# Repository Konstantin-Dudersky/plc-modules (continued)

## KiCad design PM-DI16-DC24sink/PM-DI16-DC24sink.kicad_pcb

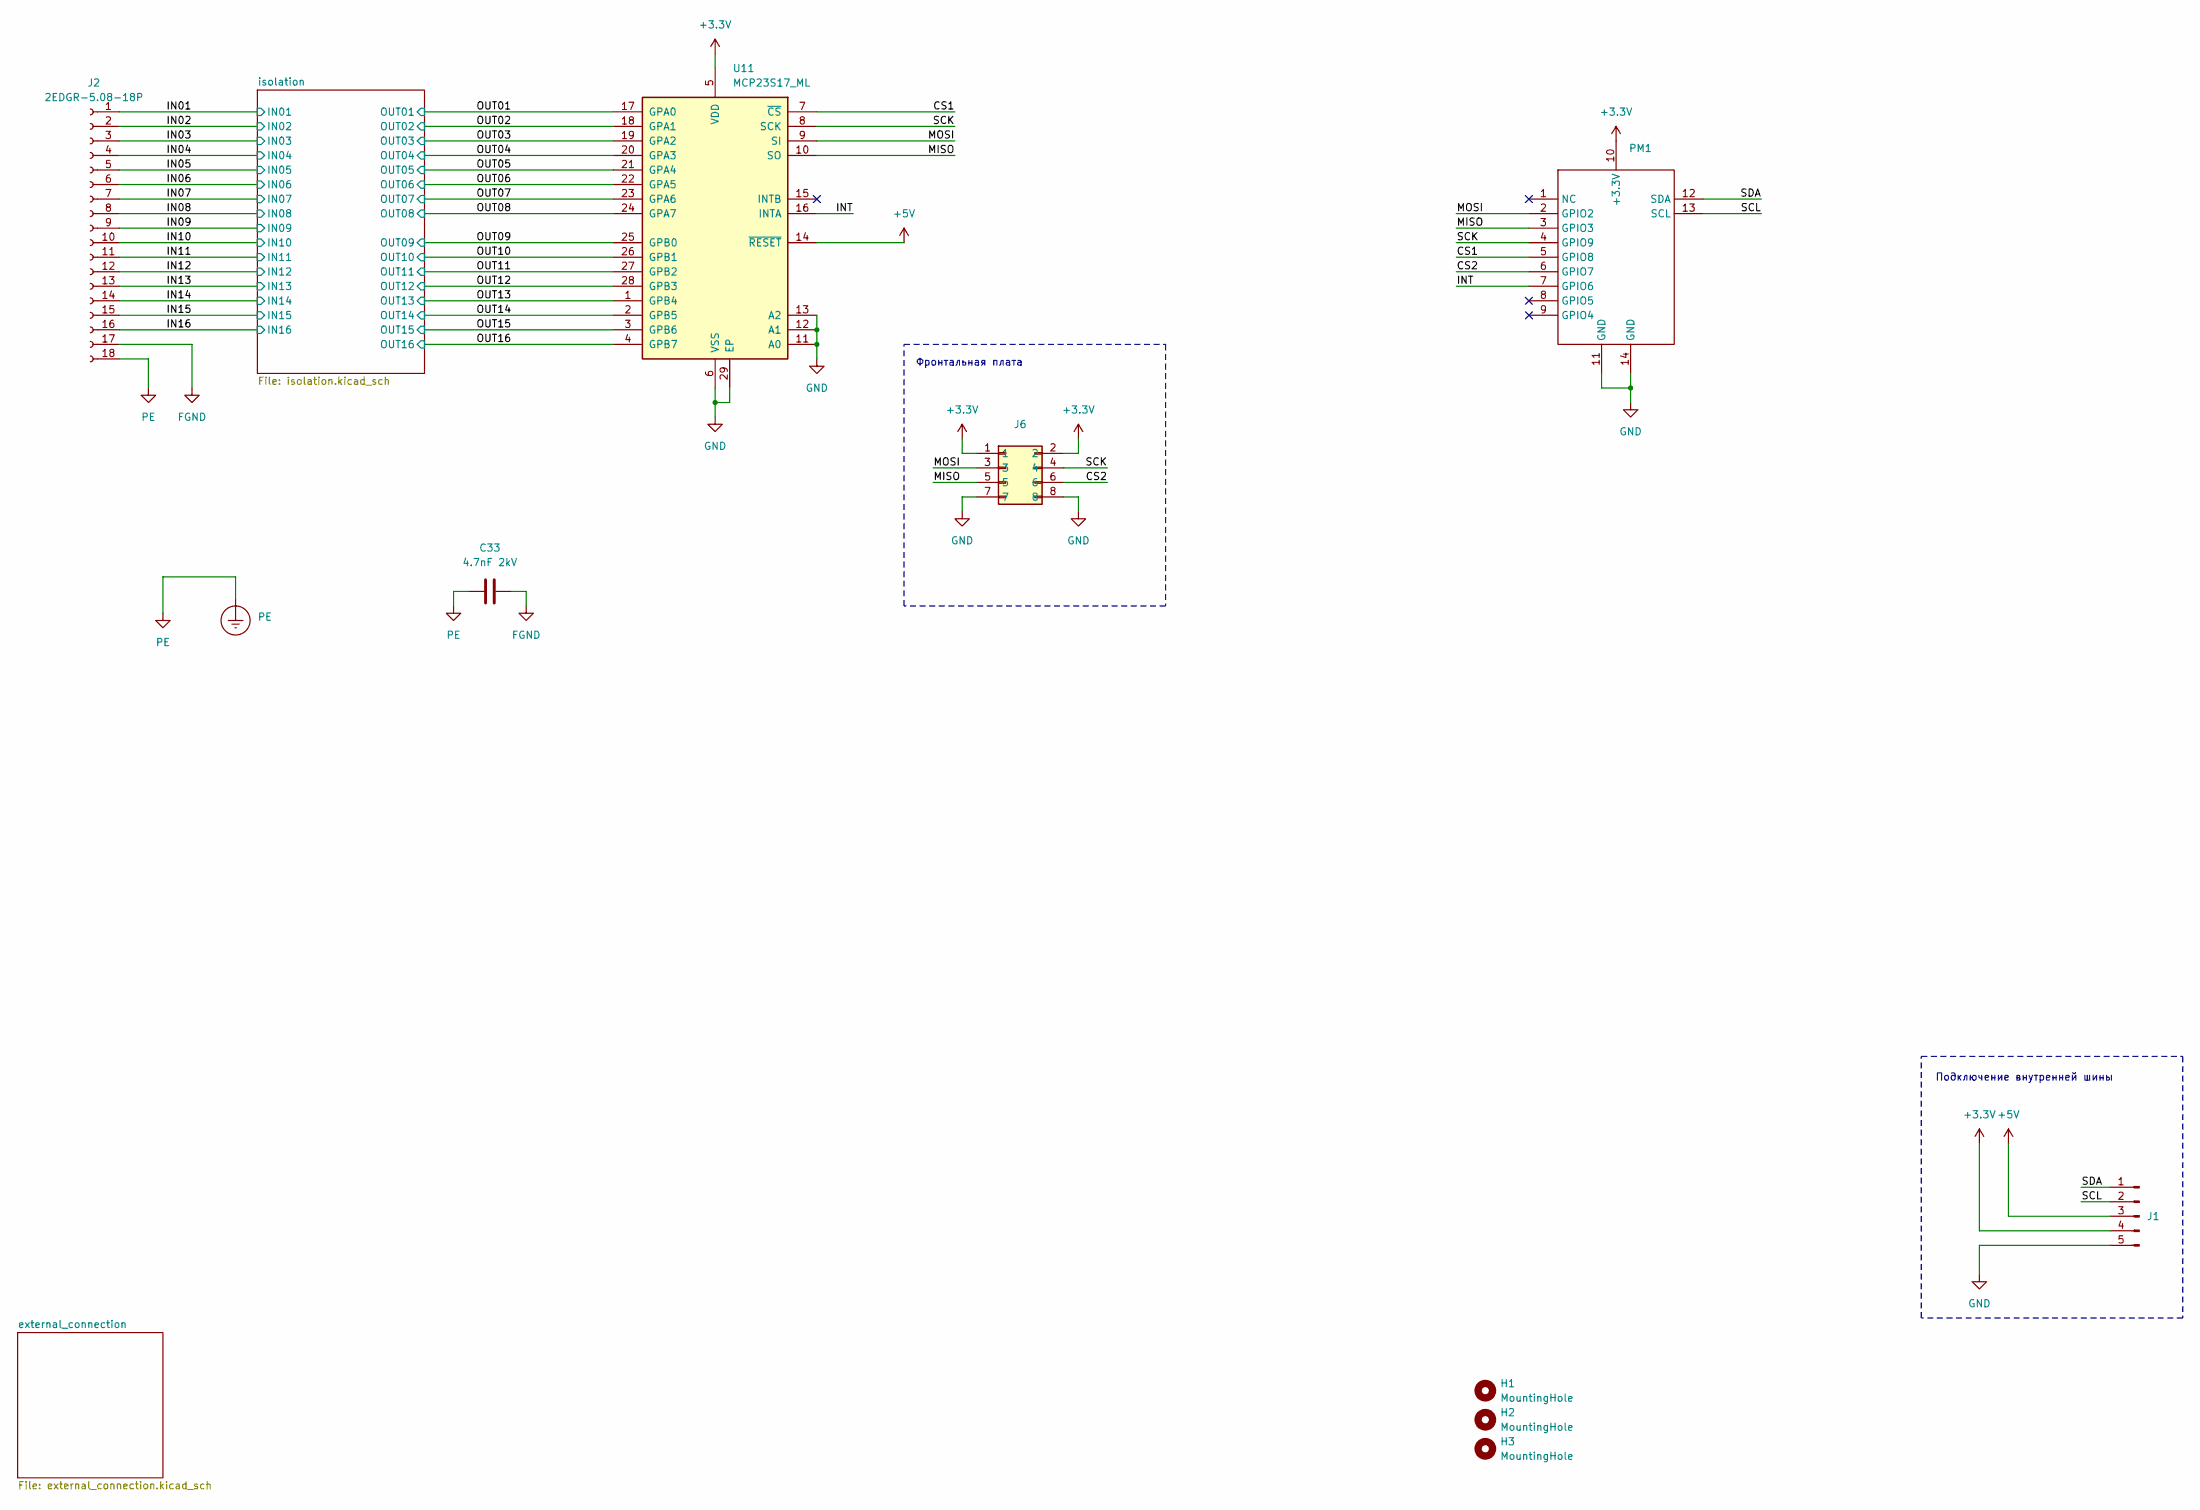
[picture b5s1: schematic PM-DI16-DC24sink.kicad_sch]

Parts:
C33: 4.7nF 2kV; C_1812_4532Metric_Pad1.57x3.40mm_HandSolder; part_ipn C_4.7nF_2kV_1812
H1, H2, H3: MountingHole; MountingHole_3.2mm_M3
J1: PinHeader_01x05_P2.54_THT_angle; PinHeader_1x05_P2.54mm_Horizontal; part_ipn PinHeader_01x05_P2.54_THT_angle
J2: 2EDGR-5.08-18P; Degson_2EDGR-5.08-18P; part_ipn 2EDGR-5.08-18P
J6: PM-front-02x04
PE1: PE
PM1: PM-ESP32C3
U11: MCP23S17_ML; QFN-28-1EP_6x6mm_P0.65mm_EP4.25x4.25mm; part_ipn MCP23S17-E/ML

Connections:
+3.3V: J1.4, J6.1, J6.2, PM1.10 (+3.3V), U11.5 (VDD)
+5V: J1.3, U11.14 (~RESET); also elsewhere on the board
/CS1: PM1.5 (GPIO8), U11.7 (~CS)
/CS2: J6.6, PM1.6 (GPIO7)
/IN01: J2.1; also elsewhere on the board
/IN02: J2.2; also elsewhere on the board
/IN03: J2.3; also elsewhere on the board
/IN04: J2.4; also elsewhere on the board
/IN05: J2.5; also elsewhere on the board
/IN06: J2.6; also elsewhere on the board
/IN07: J2.7; also elsewhere on the board
/IN08: J2.8; also elsewhere on the board
/IN09: J2.9; also elsewhere on the board
/IN10: J2.10; also elsewhere on the board
/IN11: J2.11; also elsewhere on the board
/IN12: J2.12; also elsewhere on the board
/IN13: J2.13; also elsewhere on the board
/IN14: J2.14; also elsewhere on the board
/IN15: J2.15; also elsewhere on the board
/IN16: J2.16; also elsewhere on the board
/INT: PM1.7 (GPIO6), U11.16 (INTA)
/MISO: J6.5, PM1.3 (GPIO3), U11.10 (SO)
/MOSI: J6.3, PM1.2 (GPIO2), U11.9 (SI)
/OUT01: U11.17 (GPA0); also elsewhere on the board
/OUT02: U11.18 (GPA1); also elsewhere on the board
/OUT03: U11.19 (GPA2); also elsewhere on the board
/OUT04: U11.20 (GPA3); also elsewhere on the board
/OUT05: U11.21 (GPA4); also elsewhere on the board
/OUT06: U11.22 (GPA5); also elsewhere on the board
/OUT07: U11.23 (GPA6); also elsewhere on the board
/OUT08: U11.24 (GPA7); also elsewhere on the board
/OUT09: U11.25 (GPB0); also elsewhere on the board
/OUT10: U11.26 (GPB1); also elsewhere on the board
/OUT11: U11.27 (GPB2); also elsewhere on the board
/OUT12: U11.28 (GPB3); also elsewhere on the board
/OUT13: U11.1 (GPB4); also elsewhere on the board
/OUT14: U11.2 (GPB5); also elsewhere on the board
/OUT15: U11.3 (GPB6); also elsewhere on the board
/OUT16: U11.4 (GPB7); also elsewhere on the board
/SCK: J6.4, PM1.4 (GPIO9), U11.8 (SCK)
/SCL: J1.2, PM1.13 (SCL)
/SDA: J1.1, PM1.12 (SDA)
FGND: C33.2, J2.17; also elsewhere on the board
GND: J1.5, J6.7, J6.8, PM1.11 (GND), PM1.14 (GND), U11.6 (VSS), U11.11 (A0), U11.12 (A1), U11.13 (A2), U11.29 (EP); also elsewhere on the board
PE: C33.1, J2.18, PE1.1

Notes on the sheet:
Фронтальная плата
Подключение внутренней шины

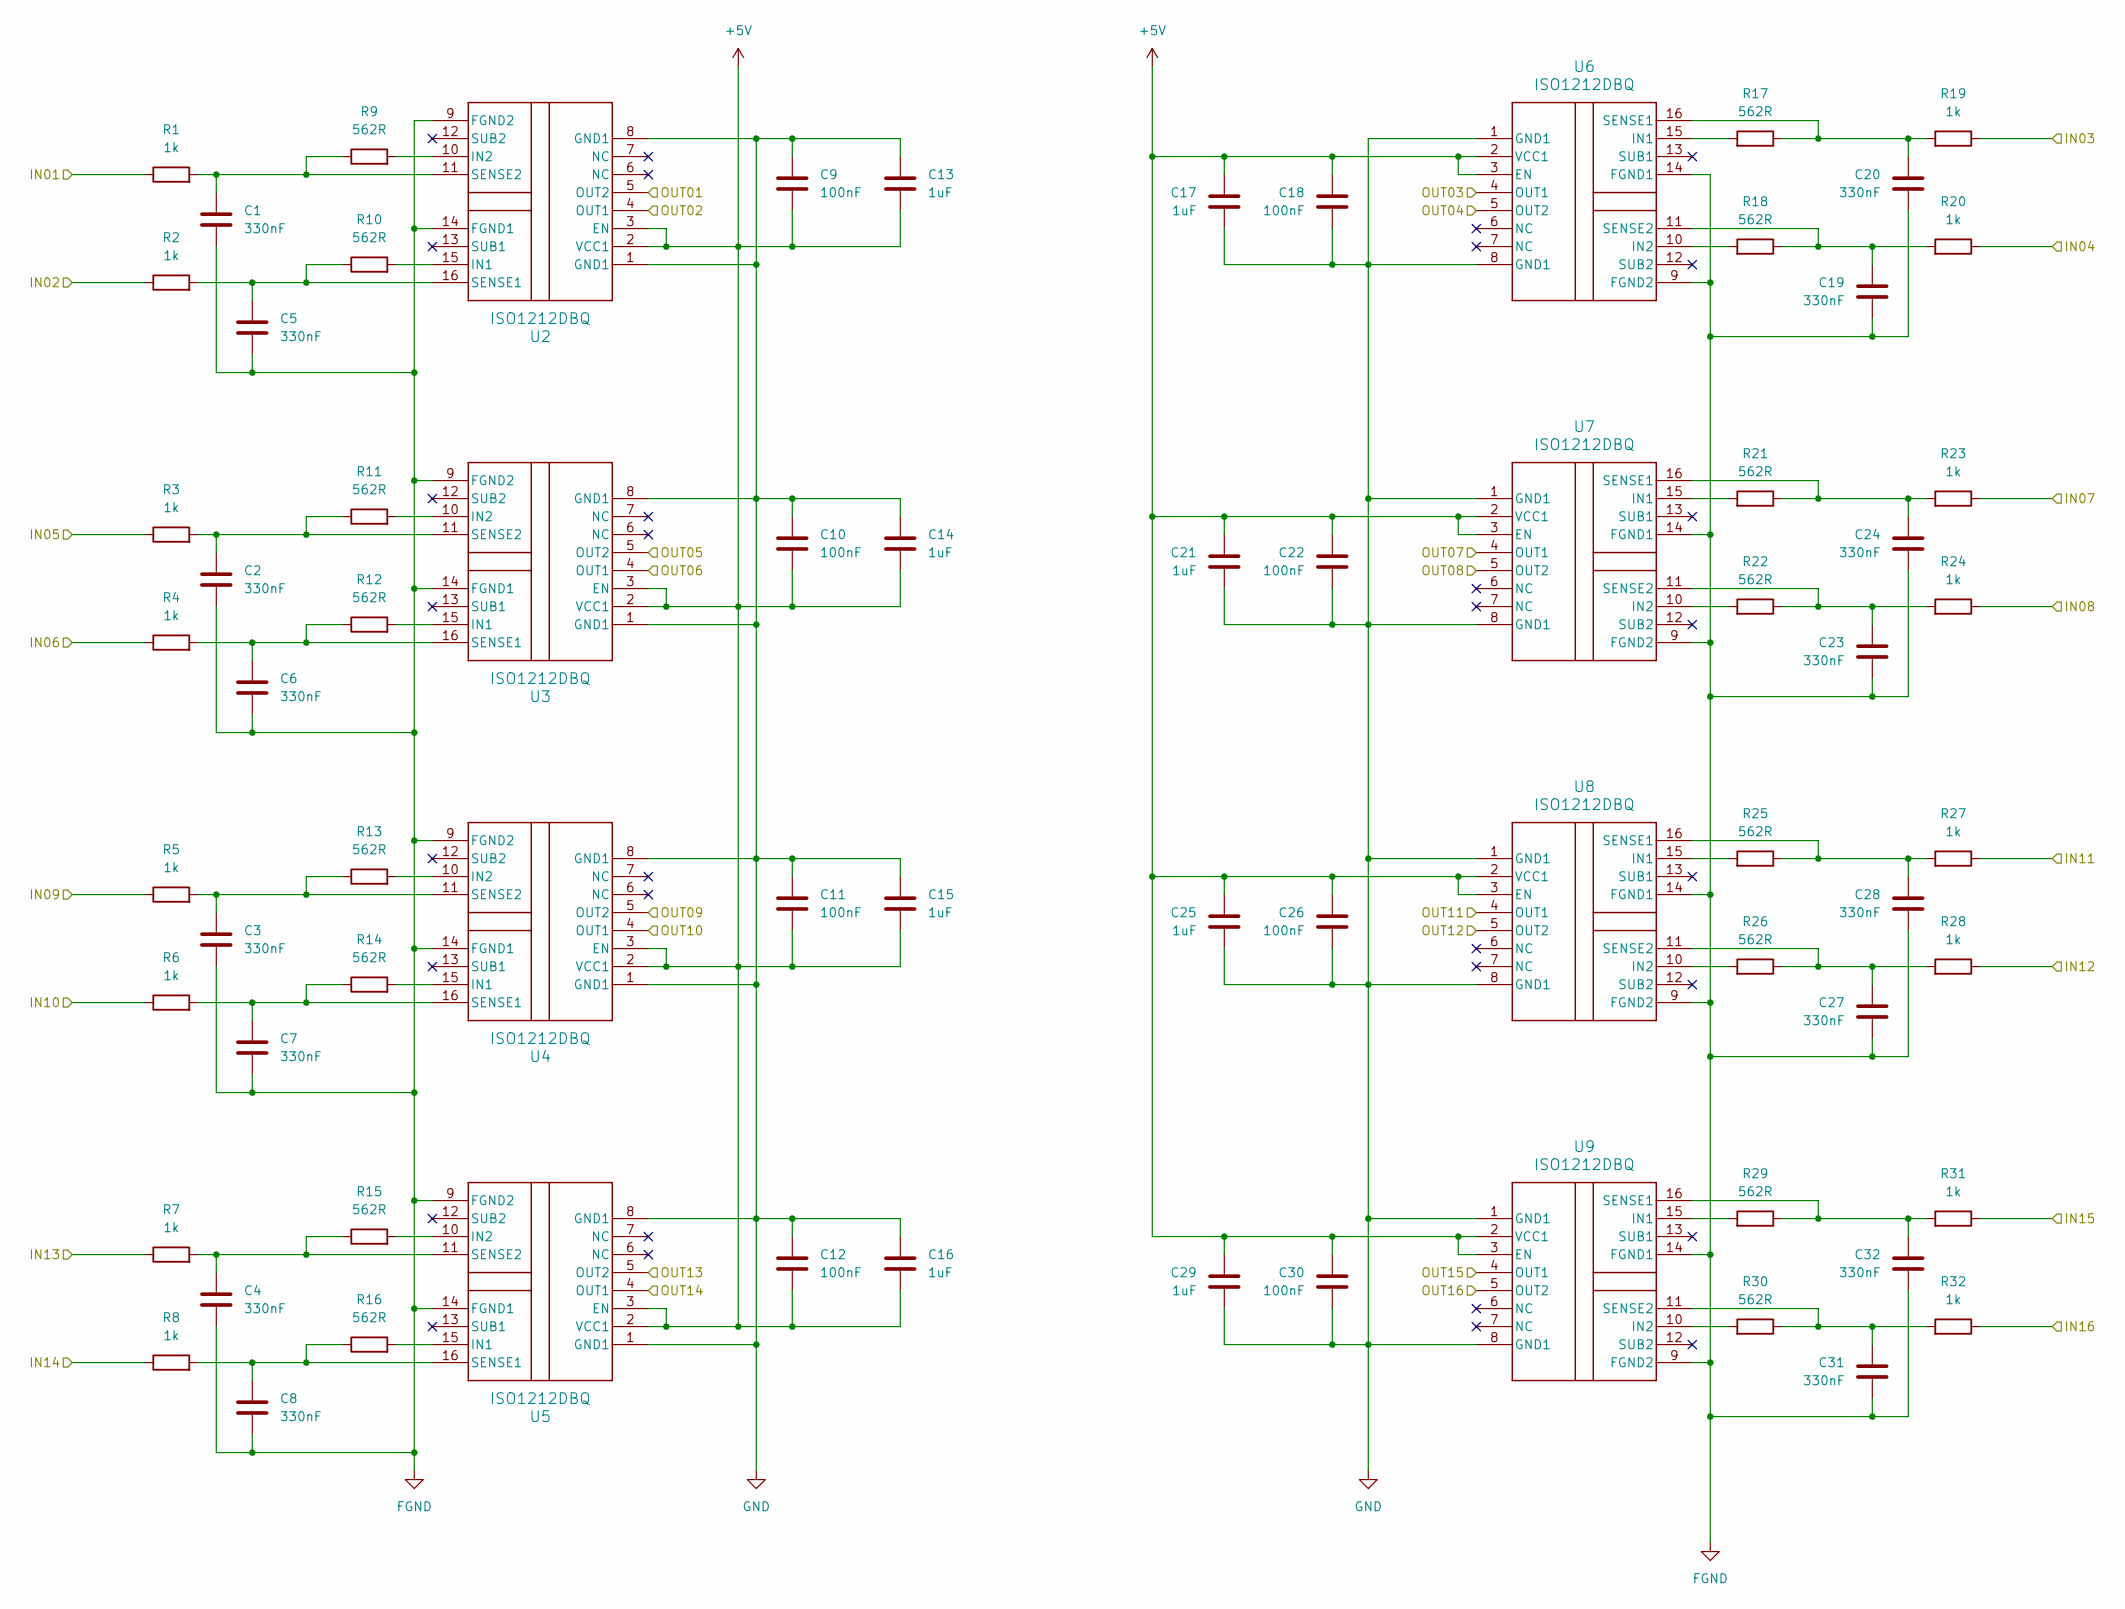
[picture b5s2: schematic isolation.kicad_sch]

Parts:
C1, C2, C3, C4, C5, C6, C7, C8, C19, C20, C23, C24, C27, C28, C31, C32: 330nF; C_1206_3216Metric_Pad1.33x1.80mm_HandSolder; part_ipn C_330nF_50V_1206
C9, C10, C11, C12, C18, C22, C26, C30: 100nF; C_1206_3216Metric_Pad1.33x1.80mm_HandSolder; part_ipn C_100nF_50V_1206
C13, C14, C15, C16, C17, C21, C25, C29: 1uF; C_1206_3216Metric_Pad1.33x1.80mm_HandSolder; part_ipn C_1uF_50V_1206
R1, R2, R3, R4, R5, R6, R7, R8, R19, R20, R23, R24, R27, R28, R31, R32: 1k; R_1206_3216Metric_Pad1.30x1.75mm_HandSolder; part_ipn R_1k_1206_1%
R9, R10, R11, R12, R13, R14, R15, R16, R17, R18, R21, R22, R25, R26, R29, R30: 562R; R_1206_3216Metric_Pad1.30x1.75mm_HandSolder; part_ipn R_562R_1206_1%
U2, U3, U4, U5, U6, U7, U8, U9: ISO1212DBQ; DBQ0016A_M; part_ipn ISO1212

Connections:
+5V: C9.2, C10.2, C11.2, C12.2, C13.2, C14.2, C15.2, C16.2, C17.1, C18.1, C21.1, C22.1, C25.1, C26.1, C29.1, C30.1, U2.2 (VCC1), U2.3 (EN), U3.2 (VCC1), U3.3 (EN), U4.2 (VCC1), U4.3 (EN), U5.2 (VCC1), U5.3 (EN), U6.2 (VCC1), U6.3 (EN), U7.2 (VCC1), U7.3 (EN), U8.2 (VCC1), U8.3 (EN), U9.2 (VCC1), U9.3 (EN); also elsewhere on the board
/IN01: R1.1; also elsewhere on the board
/IN02: R2.1; also elsewhere on the board
/IN03: R19.1; also elsewhere on the board
/IN04: R20.1; also elsewhere on the board
/IN05: R3.1; also elsewhere on the board
/IN06: R4.1; also elsewhere on the board
/IN07: R23.1; also elsewhere on the board
/IN08: R24.1; also elsewhere on the board
/IN09: R5.1; also elsewhere on the board
/IN10: R6.1; also elsewhere on the board
/IN11: R27.1; also elsewhere on the board
/IN12: R28.1; also elsewhere on the board
/IN13: R7.1; also elsewhere on the board
/IN14: R8.1; also elsewhere on the board
/IN15: R31.1; also elsewhere on the board
/IN16: R32.1; also elsewhere on the board
/OUT01: U2.5 (OUT2); also elsewhere on the board
/OUT02: U2.4 (OUT1); also elsewhere on the board
/OUT03: U6.4 (OUT1); also elsewhere on the board
/OUT04: U6.5 (OUT2); also elsewhere on the board
/OUT05: U3.5 (OUT2); also elsewhere on the board
/OUT06: U3.4 (OUT1); also elsewhere on the board
/OUT07: U7.4 (OUT1); also elsewhere on the board
/OUT08: U7.5 (OUT2); also elsewhere on the board
/OUT09: U4.5 (OUT2); also elsewhere on the board
/OUT10: U4.4 (OUT1); also elsewhere on the board
/OUT11: U8.4 (OUT1); also elsewhere on the board
/OUT12: U8.5 (OUT2); also elsewhere on the board
/OUT13: U5.5 (OUT2); also elsewhere on the board
/OUT14: U5.4 (OUT1); also elsewhere on the board
/OUT15: U9.4 (OUT1); also elsewhere on the board
/OUT16: U9.5 (OUT2); also elsewhere on the board
FGND: C1.2, C2.2, C3.2, C4.2, C5.2, C6.2, C7.2, C8.2, C19.2, C20.2, C23.2, C24.2, C27.2, C28.2, C31.2, C32.2, U2.9 (FGND2), U2.14 (FGND1), U3.9 (FGND2), U3.14 (FGND1), U4.9 (FGND2), U4.14 (FGND1), U5.9 (FGND2), U5.14 (FGND1), U6.9 (FGND2), U6.14 (FGND1), U7.9 (FGND2), U7.14 (FGND1), U8.9 (FGND2), U8.14 (FGND1), U9.9 (FGND2), U9.14 (FGND1); also elsewhere on the board
GND: C9.1, C10.1, C11.1, C12.1, C13.1, C14.1, C15.1, C16.1, C17.2, C18.2, C21.2, C22.2, C25.2, C26.2, C29.2, C30.2, U2.1 (GND1), U2.8 (GND1), U3.1 (GND1), U3.8 (GND1), U4.1 (GND1), U4.8 (GND1), U5.1 (GND1), U5.8 (GND1), U6.1 (GND1), U6.8 (GND1), U7.1 (GND1), U7.8 (GND1), U8.1 (GND1), U8.8 (GND1), U9.1 (GND1), U9.8 (GND1); also elsewhere on the board
unnamed: R10.2, U2.15 (IN1)
unnamed: R9.2, U2.10 (IN2)
unnamed: C5.1, R2.2, R10.1, U2.16 (SENSE1)
unnamed: C1.1, R1.2, R9.1, U2.11 (SENSE2)
unnamed: R12.2, U3.15 (IN1)
unnamed: R11.2, U3.10 (IN2)
unnamed: C6.1, R4.2, R12.1, U3.16 (SENSE1)
unnamed: C2.1, R3.2, R11.1, U3.11 (SENSE2)
unnamed: R14.2, U4.15 (IN1)
unnamed: R13.2, U4.10 (IN2)
unnamed: C7.1, R6.2, R14.1, U4.16 (SENSE1)
unnamed: C3.1, R5.2, R13.1, U4.11 (SENSE2)
unnamed: R16.2, U5.15 (IN1)
unnamed: R15.2, U5.10 (IN2)
unnamed: C8.1, R8.2, R16.1, U5.16 (SENSE1)
unnamed: C4.1, R7.2, R15.1, U5.11 (SENSE2)
unnamed: R17.2, U6.15 (IN1)
unnamed: R18.2, U6.10 (IN2)
unnamed: C20.1, R17.1, R19.2, U6.16 (SENSE1)
unnamed: C19.1, R18.1, R20.2, U6.11 (SENSE2)
unnamed: R21.2, U7.15 (IN1)
unnamed: R22.2, U7.10 (IN2)
unnamed: C24.1, R21.1, R23.2, U7.16 (SENSE1)
unnamed: C23.1, R22.1, R24.2, U7.11 (SENSE2)
unnamed: R25.2, U8.15 (IN1)
unnamed: R26.2, U8.10 (IN2)
unnamed: C28.1, R25.1, R27.2, U8.16 (SENSE1)
unnamed: C27.1, R26.1, R28.2, U8.11 (SENSE2)
unnamed: R29.2, U9.15 (IN1)
unnamed: R30.2, U9.10 (IN2)
unnamed: C32.1, R29.1, R31.2, U9.16 (SENSE1)
unnamed: C31.1, R30.1, R32.2, U9.11 (SENSE2)

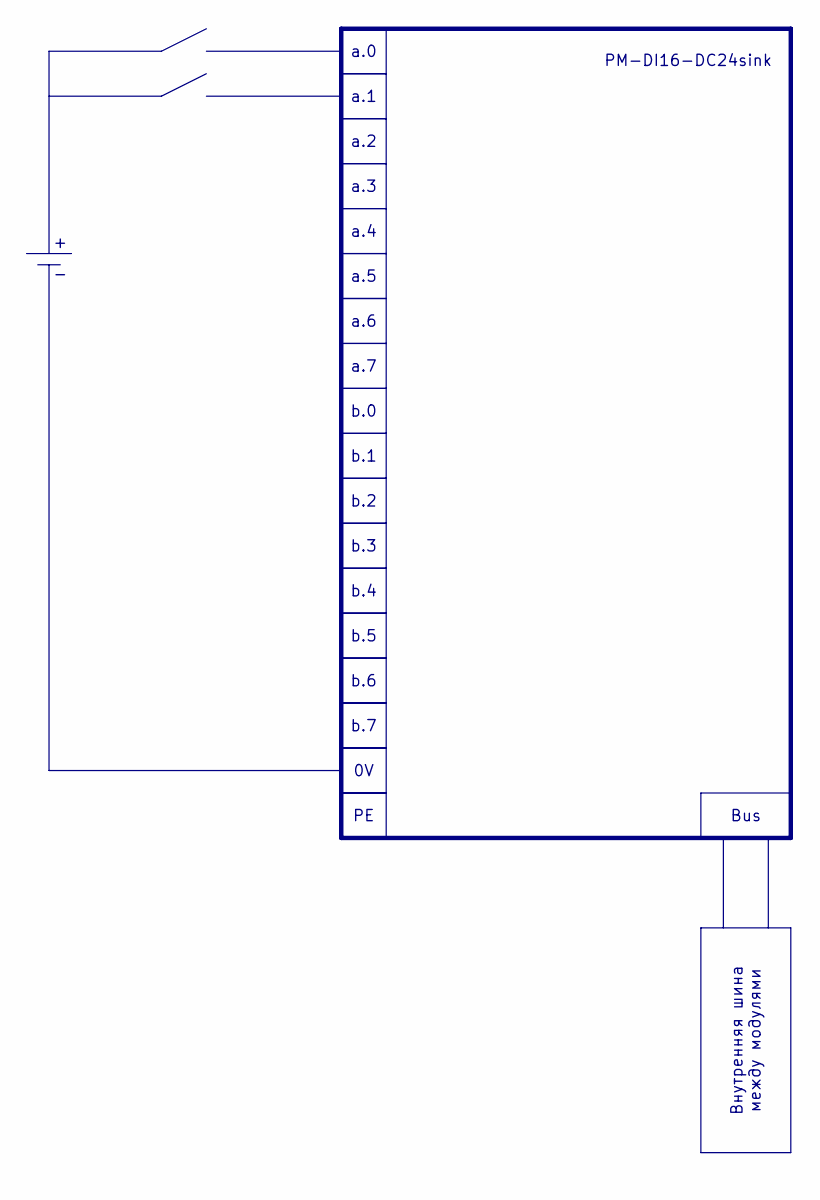
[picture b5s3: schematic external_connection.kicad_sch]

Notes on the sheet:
Внутренняя шина между модулями
b.0
b.1
b.4
b.6
a.1
a.2
Bus
b.7
b.3
a.6
a.3
a.5
b.5
b.2
a.0
a.4
a.7
PM-DI16-DC24sink

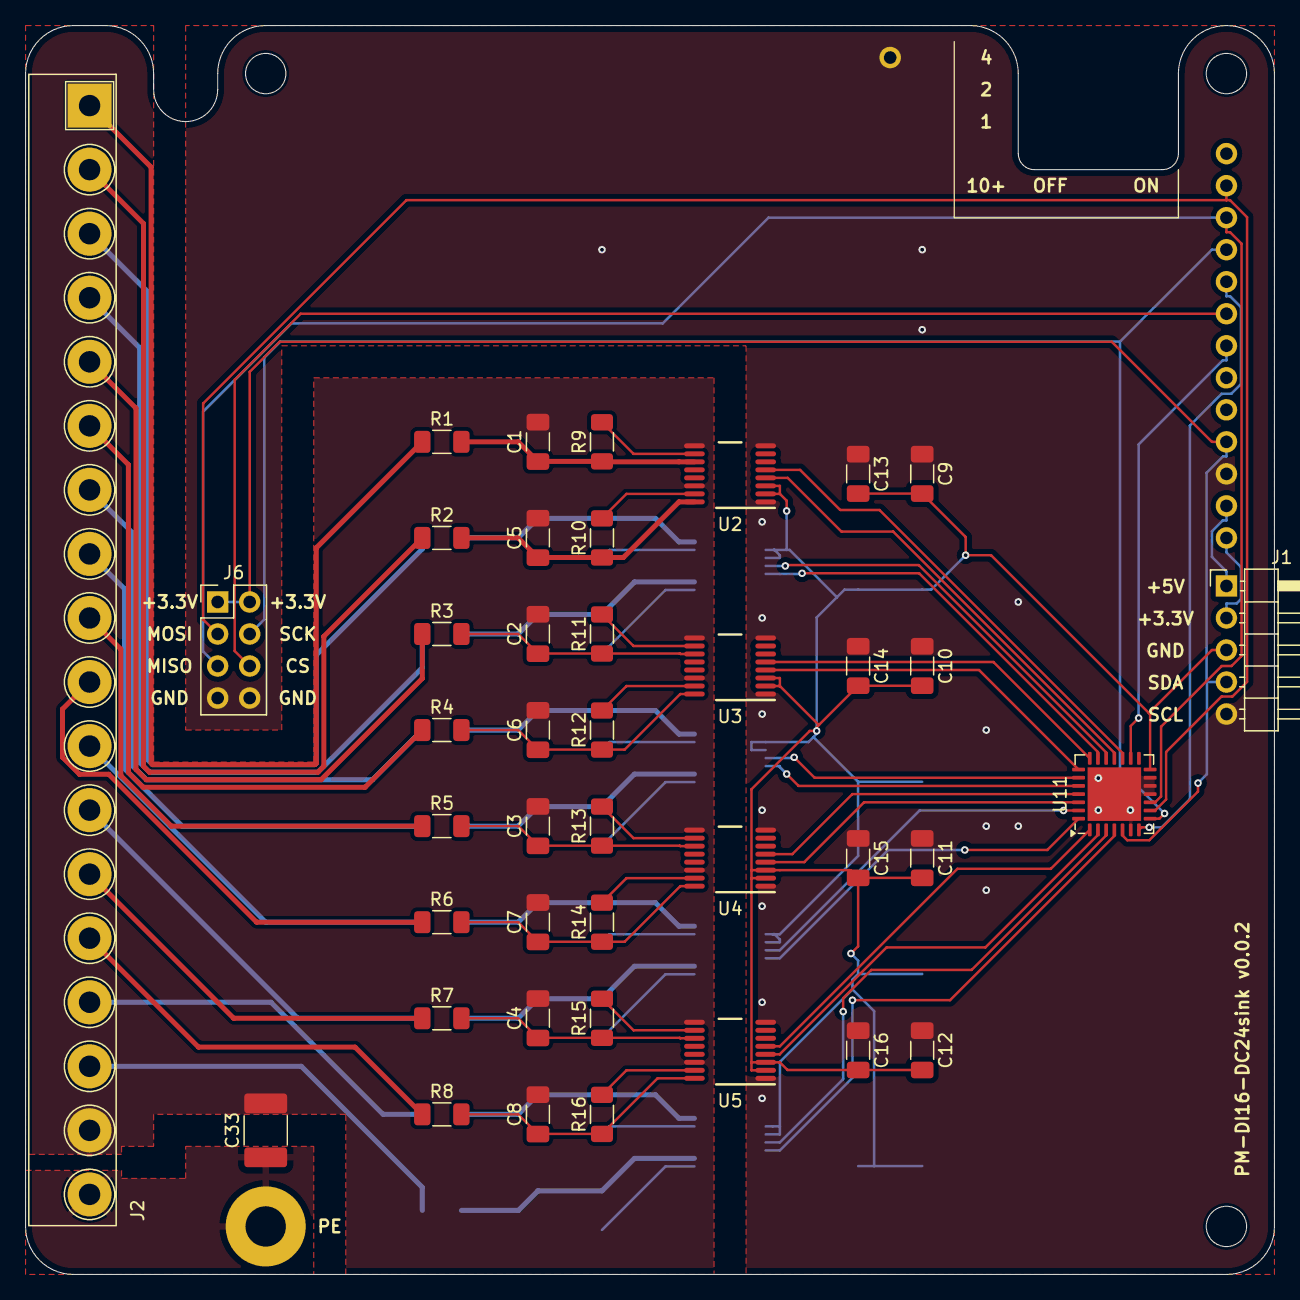
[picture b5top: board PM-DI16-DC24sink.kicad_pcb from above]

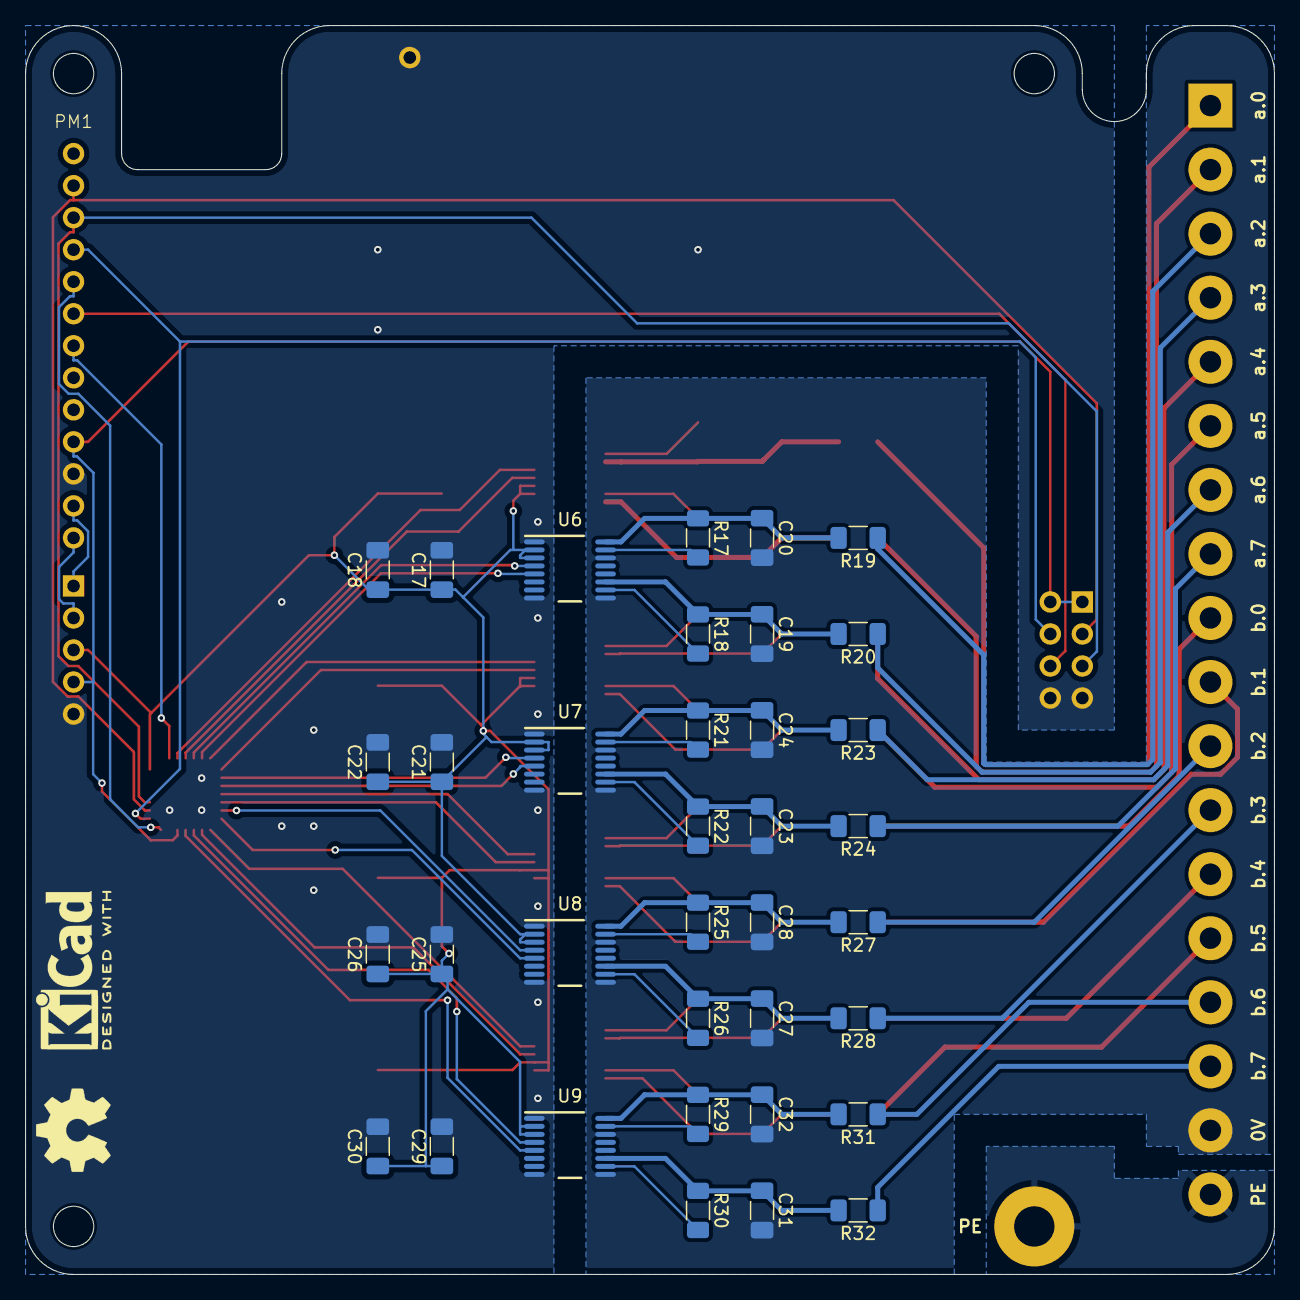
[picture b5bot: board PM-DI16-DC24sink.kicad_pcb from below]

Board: 2 copper layers, 99.1 x 99.1 mm, 84 parts (39 on the bottom side), 77 nets.

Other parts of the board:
kicad_logo: KiCad-Logo2_5mm_SilkScreen
oshw_logo: OSHW-Symbol_6.7x6mm_SilkScreen
